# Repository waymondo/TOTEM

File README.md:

<picture align="center">
  <source media="(prefers-color-scheme: dark)" srcset="/docs/images/TOTEM_logo_dark.svg">
  <source media="(prefers-color-scheme: light)" srcset="/docs/images/TOTEM_logo_bright.svg">
  
</picture>

<h1 align="center">T O T E M</h1>

TOTEM is a 38 key column-staggered choc split keyboard. It is meant to be used with a [Seeed Studio XIAO nRF52840 BLE](https://www.seeedstudio.com/Seeed-XIAO-BLE-nRF52840-p-5201.html) or [XIAO RP2040](https://www.seeedstudio.com/XIAO-RP2040-v1-0-p-5026.html).
It was created for the SEEED XIAO keyboard contest.\
[Here](https://www.hackster.io/geist/totem-a-tiny-splitkeyboard-with-splay-cb2e43) you can read about the process of making it.

***

## LAYOUT

***

## 42-KEY VARIANT (WORK IN PROGRESS)

This fork adds four keys to the TOTEM: one key above each outer pinky key (same 10° tilted column, one 17 mm pitch up) and one extra outer thumb key per side (continuing the thumb arc at 15°). The new keys form a sixth matrix column on XIAO pin D7 (`P1.12`, the former TRRS RX line), so this variant is meant for a wireless build with the XIAO nRF52840, where the TRRS jack is not populated.

What is done in the KiCad project ([PCB/totem_0-3](/PCB/totem_0-3/)):

- schematic: `SWL20/SWL21`, `SWR20/SWR21` with diodes `DL20/DL21`, `DR20/DR21` on `COL5_L`/`COL5_R`, XIAO pin 8 relabelled from `RX` to `COL5`, TRRS RX pin marked no-connect
- PCB: the switch and diode footprints are placed with their nets assigned, and the old RX traces are removed

What is still left to do in KiCad before ordering boards:

- route `COL5_L`/`COL5_R` and the four new diode nets, and re-route the existing tracks that now run under the new footprints
- extend the board outline (`Edge.Cuts`) around the new pinky and thumb keys, then refill the ground zones
- move the back-side silkscreen text that now sits under the new left thumb key
- regenerate the Gerbers and PDFs; the case STEP files also need to be re-modelled for the larger outline

Firmware for this variant is an [RMK](https://rmk.rs/) project in [firmware/RMK/totem](/firmware/RMK/totem/).

***

## PCB

[Here](/PCB/) you can find the KiCad files and Gerbers for the TOTEM.

***

## CASE

You can use the TOTEM without a case, but [here](/case/) you can find one I made for it.

***

## BUILD GUIDE

The build guide for the TOTEM can be found [here](/docs/buildguide.md).

***

## FIRMWARE

[QMK (VIAL) precompiled](/firmware/QMK/) or [QMK (VIAL) source](/firmware/QMK/VIAL_source/) for the TOTEM (wired using the XIAO RP2040)\
[ZMK precompiled](/firmware/ZMK/) or [ZMK source (outdated)](https://github.com/GEIGEIGEIST/zmk-config-totem) for the TOTEM (wireless using the XIAO BLE)\
[RMK source](/firmware/RMK/totem/) for the 42-key variant (wireless using the XIAO nRF52840)

***

## BUY

You can buy TOTEM kits and finished builds on [keeb.supply](https://keeb.supply/products/geist-totem) (based in Germany)

***

## PHOTOS

This is the TOTEM in a black resin case

\
\

This is the TOTEM with a black resin tenting bottom plate

\
[Video by *Wolfgang's Channel* showing the tenting system in action](https://youtu.be/rvM2BthjEI4?si=mTJVdPeZstshnDyo)

***

## CREDITS

### INSPIRATION

I've added the additional pinky key to make the TOTEM compatible with the layout boards like the [Balbuzard](https://github.com/brow/balbuzard) by [Tom Brow](https://github.com/brow) and the [Osprette](https://github.com/smores56/osprette) by [Sam Mohr](https://github.com/smores56) use, where you put the keybinding of the top left and right keys on an outer pinky key.

### HELP FIXING THINGS

People who helped me create this board and fix stuff

#### PCB
- [Marco "Bob"](https://github.com/GroooveBob)

#### CASE
- [Freya](https://github.com/freya-irl)
- [Bubbleology](https://github.com/bubbleology)

#### FIRMWARE
- [Cem Aksoylar](https://github.com/caksoylar)
- [Grinnie](https://github.com/regicidalplutophage)
- [Alaa Saad Mansour](https://github.com/AlaaSaadAbdo)
- [pekudzu](https://github.com/pekudzu)

If you build a TOTEM I would be pretty happy to see some pictures. And if you want to leave me a tip you can do this [here](https://ko-fi.com/geigeigeist) (but please don't feel pressured)

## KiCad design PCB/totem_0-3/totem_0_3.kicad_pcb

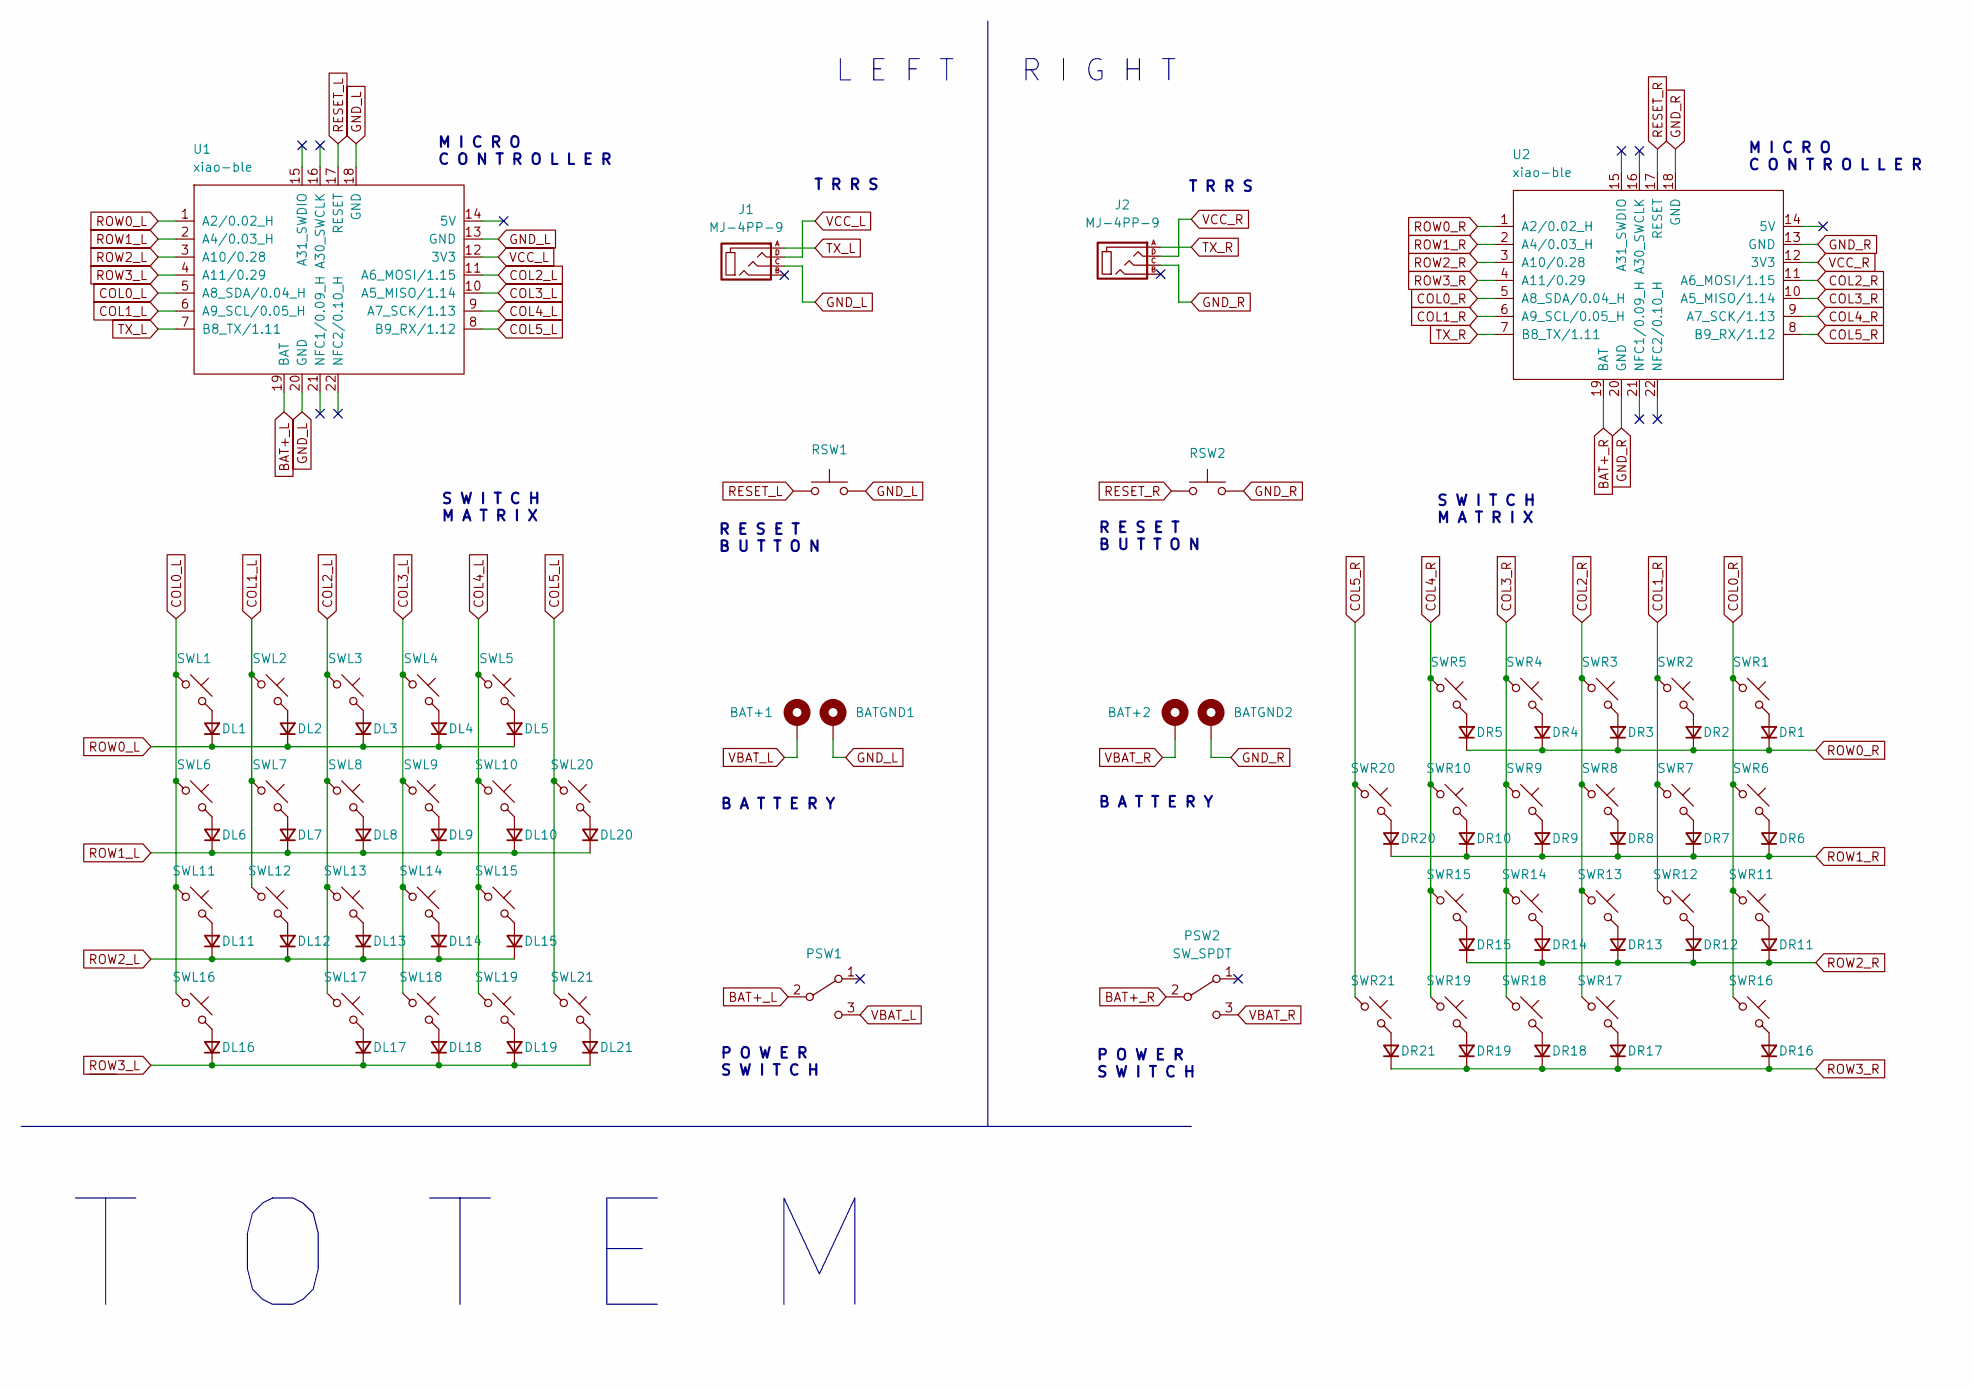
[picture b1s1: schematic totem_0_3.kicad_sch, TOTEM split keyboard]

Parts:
BAT+1, BAT+2: +; BatteryPad
BATGND1, BATGND2: -; BatteryPad
DL1, DL2, DL3, DL4, DL5, DL6, DL7, DL8, DL9, DL10, DL11, DL12, DL13, DL14, DL15, DL16, DL17, DL18, DL19, DL20, DL21: D_Small; Diode_SOD123
DR1, DR2, DR3, DR4, DR5, DR6, DR7, DR8, DR9, DR10, DR11, DR12, DR13, DR14, DR15, DR16, DR17, DR18, DR19, DR20, DR21: D_Small; Diode_SOD123
J1, J2: MJ-4PP-9; MJ-4PP-9_1side
PSW1, PSW2: SW_SPDT; MSK12C02
RSW1, RSW2: SW_Push; SKHLLCA010
SWL1, SWL2, SWL3, SWL4, SWL5, SWL6, SWL7, SWL8, SWL9, SWL10, SWL11, SWL12, SWL13, SWL14, SWL15, SWL16, SWL17, SWL18, SWL19, SWL20, SWL21: SW_Push_45deg; Kailh_socket_PG1350_optional
SWR1, SWR2, SWR3, SWR4, SWR5, SWR6, SWR7, SWR8, SWR9, SWR10, SWR11, SWR12, SWR13, SWR14, SWR15, SWR16, SWR17, SWR18, SWR19, SWR20, SWR21: SW_Push_45deg; Kailh_socket_PG1350_optional
U1, U2: xiao-ble; xiao-ble-smd-cutout

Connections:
BAT+_L: PSW1.2 (B), U1.19 (BAT); also elsewhere on the board
BAT+_R: PSW2.2 (B), U2.19 (BAT); also elsewhere on the board
COL0_L: SWL1.1, SWL6.1, SWL11.1, SWL16.1, U1.5 (A8_SDA/0.04_H)
COL0_R: SWR1.1, SWR6.1, SWR11.1, SWR16.1, U2.5 (A8_SDA/0.04_H)
COL1_L: SWL2.1, SWL7.1, SWL12.1, U1.6 (A9_SCL/0.05_H)
COL1_R: SWR2.1, SWR7.1, SWR12.1, U2.6 (A9_SCL/0.05_H)
COL2_L: SWL3.1, SWL8.1, SWL13.1, SWL17.1, U1.11 (A6_MOSI/1.15)
COL2_R: SWR3.1, SWR8.1, SWR13.1, SWR17.1, U2.11 (A6_MOSI/1.15)
COL3_L: SWL4.1, SWL9.1, SWL14.1, SWL18.1, U1.10 (A5_MISO/1.14)
COL3_R: SWR4.1, SWR9.1, SWR14.1, SWR18.1, U2.10 (A5_MISO/1.14)
COL4_L: SWL5.1, SWL10.1, SWL15.1, SWL19.1, U1.9 (A7_SCK/1.13)
COL4_R: SWR5.1, SWR10.1, SWR15.1, SWR19.1, U2.9 (A7_SCK/1.13)
COL5_L: SWL20.1, SWL21.1, U1.8 (B9_RX/1.12)
COL5_R: SWR20.1, SWR21.1, U2.8 (B9_RX/1.12)
GND_L: BATGND1.1, J1.C, RSW1.2, U1.13 (GND), U1.18 (GND), U1.20 (GND)
GND_R: BATGND2.1, J2.C, RSW2.2, U2.13 (GND), U2.18 (GND), U2.20 (GND); also elsewhere on the board
unnamed: DL1.2 (A), SWL1.2
unnamed: DL2.2 (A), SWL2.2
unnamed: DL3.2 (A), SWL3.2
unnamed: DL4.2 (A), SWL4.2
unnamed: DL5.2 (A), SWL5.2
unnamed: DL6.2 (A), SWL6.2
unnamed: DL7.2 (A), SWL7.2
unnamed: DL8.2 (A), SWL8.2
unnamed: DL9.2 (A), SWL9.2
unnamed: DL10.2 (A), SWL10.2
unnamed: DL11.2 (A), SWL11.2
unnamed: DL12.2 (A), SWL12.2
unnamed: DL13.2 (A), SWL13.2
unnamed: DL14.2 (A), SWL14.2
unnamed: DL15.2 (A), SWL15.2
unnamed: DL16.2 (A), SWL16.2
unnamed: DL17.2 (A), SWL17.2
unnamed: DL18.2 (A), SWL18.2
unnamed: DL19.2 (A), SWL19.2
unnamed: DL20.2 (A), SWL20.2
unnamed: DL21.2 (A), SWL21.2
unnamed: DR1.2 (A), SWR1.2
unnamed: DR2.2 (A), SWR2.2
unnamed: DR3.2 (A), SWR3.2
unnamed: DR4.2 (A), SWR4.2
unnamed: DR5.2 (A), SWR5.2
unnamed: DR6.2 (A), SWR6.2
unnamed: DR7.2 (A), SWR7.2
unnamed: DR8.2 (A), SWR8.2
unnamed: DR9.2 (A), SWR9.2
unnamed: DR10.2 (A), SWR10.2
unnamed: DR11.2 (A), SWR11.2
unnamed: DR12.2 (A), SWR12.2
unnamed: DR13.2 (A), SWR13.2
unnamed: DR14.2 (A), SWR14.2
unnamed: DR15.2 (A), SWR15.2
unnamed: DR16.2 (A), SWR16.2
unnamed: DR17.2 (A), SWR17.2
unnamed: DR18.2 (A), SWR18.2
unnamed: DR19.2 (A), SWR19.2
unnamed: DR20.2 (A), SWR20.2
unnamed: DR21.2 (A), SWR21.2
RESET_L: RSW1.1, U1.17 (RESET)
RESET_R: RSW2.1, U2.17 (RESET); also elsewhere on the board
ROW0_L: DL1.1 (K), DL2.1 (K), DL3.1 (K), DL4.1 (K), DL5.1 (K), U1.1 (A2/0.02_H)
ROW0_R: DR1.1 (K), DR2.1 (K), DR3.1 (K), DR4.1 (K), DR5.1 (K), U2.1 (A2/0.02_H)
ROW1_L: DL6.1 (K), DL7.1 (K), DL8.1 (K), DL9.1 (K), DL10.1 (K), DL20.1 (K), U1.2 (A4/0.03_H)
ROW1_R: DR6.1 (K), DR7.1 (K), DR8.1 (K), DR9.1 (K), DR10.1 (K), DR20.1 (K), U2.2 (A4/0.03_H)
ROW2_L: DL11.1 (K), DL12.1 (K), DL13.1 (K), DL14.1 (K), DL15.1 (K), U1.3 (A10/0.28)
ROW2_R: DR11.1 (K), DR12.1 (K), DR13.1 (K), DR14.1 (K), DR15.1 (K), U2.3 (A10/0.28)
ROW3_L: DL16.1 (K), DL17.1 (K), DL18.1 (K), DL19.1 (K), DL21.1 (K), U1.4 (A11/0.29)
ROW3_R: DR16.1 (K), DR17.1 (K), DR18.1 (K), DR19.1 (K), DR21.1 (K), U2.4 (A11/0.29)
TX_L: J1.A, U1.7 (B8_TX/1.11)
TX_R: J2.A, U2.7 (B8_TX/1.11)
VBAT_L: BAT+1.1, PSW1.3 (C); also elsewhere on the board
VBAT_R: BAT+2.1, PSW2.3 (C); also elsewhere on the board
VCC_L: J1.D, U1.12 (3V3)
VCC_R: J2.D, U2.12 (3V3)

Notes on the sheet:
M I C R O C O N T R O L L E R
T R R S
R E S E T B U T T O N
S W I T C H M A T R I X
P O W E R S W I T C H
T O T E M
B A T T E R Y
R I G H T
L E F T

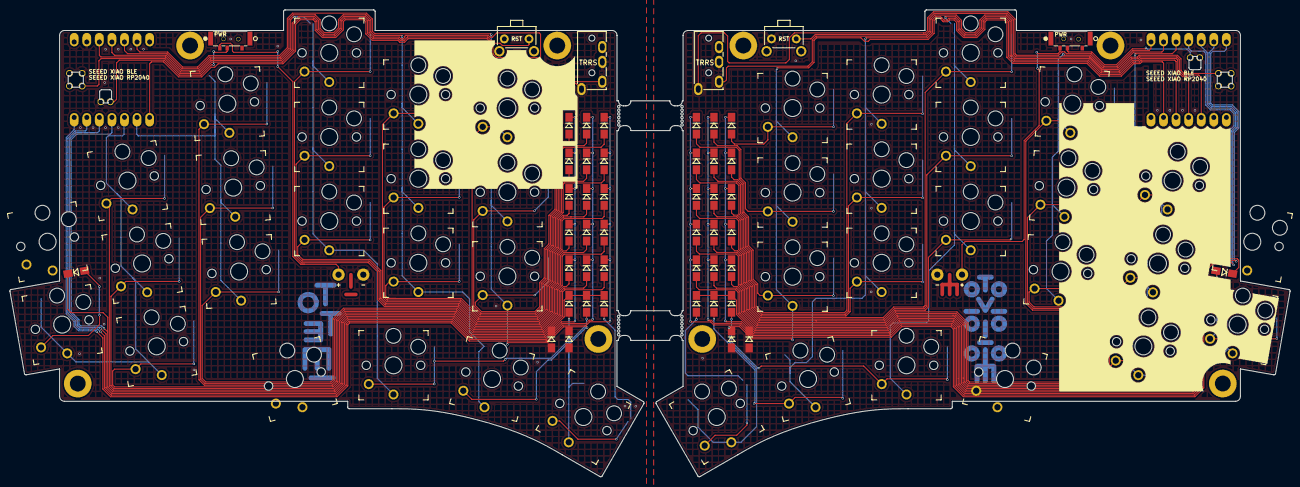
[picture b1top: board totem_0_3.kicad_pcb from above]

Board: 2 copper layers, 258.7 x 94.4 mm, 96 parts (0 on the bottom side), 74 nets.

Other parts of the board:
PWR: SW_SPDT; MSK12C02
PWR#2: SW_SPDT; MSK12C02
RST: SW_Push; SKHLLCA010

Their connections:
BAT+_L: PWR.2 (B); also elsewhere on the board
BAT+_R: PWR#2.2 (B); also elsewhere on the board
GND_R: RST.2; also elsewhere on the board
RESET_R: RST.1; also elsewhere on the board
VBAT_L: PWR.3 (C); also elsewhere on the board
VBAT_R: PWR#2.3 (C); also elsewhere on the board
